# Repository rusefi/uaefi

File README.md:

# Ultra Affordable EFI

🟢[$275 base model rusEFI store](https://www.shop.rusefi.com/shop/p/uaefi-ultra-affordable-efi)🟢

## Community Support

🔴Community support ONLY 🔴 https://www.facebook.com/groups/rusEfi 🔴 [Discord](https://github.com/rusefi/rusefi/wiki/Discord)🔴 [Commercial Support](https://www.shop.rusefi.com/shop/p/details-about-rusefi-ecu-technical-support) 🔴

## Technical Details

Open Source KiCAD hardware powered by [Hellen-One](https://github.com/andreika-git/hellen-one)

Powered by [rusEFI firmware](https://github.com/rusefi/rusefi)

[User Documentation](https://github.com/rusefi/rusefi/wiki/uaEFI)

## MCU options

1mb of flash is _required_.

One day we shall try https://jlcpcb.com/partdetail/Stmicroelectronics-STM32F427VIT6%2FC57097#EC or https://jlcpcb.com/partdetail/Stmicroelectronics-STM32F437VIT7%2FC1338578#EC

## HOWTO JLCPCB

You would need three files from ``boards/uaefi-a/board`` folder to place your JLCPB Assembly order: gerber.zip BOM-JLC.csv and CPL.csv

### Q: having trouble with opening uaefi board project. library path seems ok, i do not know how to solve missing modules issue

A: missing modules are closed source. they are filled in by github magic
github magic combines gerbers and spits out a complete bom/pcl/new gerbers to upload to jlc/friends. See https://github.com/rusefi/hellen-one/tree/master?tab=readme-ov-file#tldr for more info

### Q: Magic modules? How do I see schematics of those?

A: https://github.com/rusefi/hellen-one has full documentation for each module

### Q: Something wrong with BOM?

A: Nope, that's normal nothing to worry about click 'Continue'.

### Q: how do I get more RAM for Lua?

A: fabricate with STM32F42xVI firmware would defect extra RAM and give you extra Lua. Once your script does not fit into STM32F42xVI it's F7 time or help us leverage F413.

### Q: I've place an order with JLCPCB and I see scary looking wrong orientation?

A: that's expected. See [boards/uaefi-c/board](boards/uaefi-c/board) ``Original*.png`` files and ``Produce*.png`` after JLCPCB manual review process.

## Bluetooth power issue fix

It was found that board with installed BT module may be affected by power issue.

During power on BT module consume too much inrush current on 3.3V line causing 3.3V drop below MCU reset hreshold. This may lead to unstable start or infinity reset loop.

To fix this please install additional capacitors to 5V and 3.3V powerlines.

Polarized electrolytic capacitors with at least 10V rating and extended temperature range are recommended. Tantalum and solid electrolytic capacitors are also suitable.

**Please carefully follow illustrated polarity.**

33..47uF should be added to 5V powerrail. [This](https://www.digikey.com/en/products/detail/w%C3%BCrth-elektronik/860020372004/5727028) or [this](https://www.digikey.com/en/products/detail/w%C3%BCrth-elektronik/860080372001/5727224) or [any of these](https://www.digikey.com/en/products/filter/aluminum-electrolytic-capacitors/58?s=N4IgjCBcpgbFoDGUBmBDANgZwKYBoQB7KAbRAGYBOAJnOoAYQBdAgBwBcoQBldgJwCWAOwDmIAL4FYlBCGSR02fEVIgALGDAAOSgHZmbTpB79hYyeEo7Z8xbgLFIZRkwsM1M6HNSZ7Kp%2Bq6AAQArQBiBiAcXACqQgLsAPIoALI4aFgArnw4EgQMup5IPkoOqnBBAGqR0cZxCclpGdm5FgC01DZQ-JnKjmQArMzibqpqwZkoQXAAbsNAA).

And 220..470uF should be added to 3.3V powerrail. [This](https://www.digikey.com/en/products/detail/w%C3%BCrth-elektronik/860010273011/5726952) or [this](https://www.digikey.com/en/products/detail/w%C3%BCrth-elektronik/860020273011/5727148) or [any of these](https://www.digikey.com/en/products/filter/aluminum-electrolytic-capacitors/58?s=N4IgjCBcpgbFoDGUBmBDANgZwKYBoQB7KAbRAGYBOAJnOoAYQBdAgBwBcoQBldgJwCWAOwDmIAL4FYlBCGSR02fEVIgALGDAAOSgHZmbTpB79hYyeEo7Z8xbgLFIZRkwsM1M6HNSZ7Kp%2Bq69AAEAK0AYgYgHFwAqkIC7ADyKACyOGhYAK58OBIEDLqeSD5KDqpgIQBqUTHG8Ykp6Zk5eRYAtNQ2UPxZyo5kAKzM4qNAA).

## HOWTO EGT chip

This board has a placeholder for MAX31855 (or MAX6675) termocouple-to-digital chip. **This chip is not populated by default!**

D8 is **optional** ESD protection and also is not populated by default. You need to solder U4 only, D8 is optional. All passive components are already populated.

**MAX31855** works without addtional modification.

For **MAX6675** connect EGT- to GNDA either on J2 "C" connector or just short C28 (replace with 0R).

## [EXPERIMENTAL] How to make MAX9924 work with low tooth count trigger wheel

In some cases user may need two VR inputs on UAEFI and both trigger wheels are low-tooth count.

In default configuration MAX9924 does not work with low count trigger wheels because of its "adaptive peak threshold" and its watchdog.

On UAEFI MAX9924 is configured in **A2 mode**.

**B mode** allow use of MAX9924 with low count trigger wheels. But external Bias and Thresholt voltages should be allpied. Both can be sources from UAEFI Discrete VR module.

List of modifications:
1. pin 6: ZERO_EN connect to VCC instead of GND.
2. pin 4: supply 2.5 V instead of GND
3. pin 8: EXT, supply external threshold voltage

Pins 4 and 6 needs to be lifted from PCB to be disconnected from GND. Pin 8 initially is not connected to any circuit.

Use hot air gun to de-solder whole chip. Then twist pins 4 and 6 up so both do not touch PCB. Then solder chip back to PCB

Now use thin wire to connect:
1. pin 6 to pin 10 of the same chip.
2. pin 4 to **Vref** at R769 + C754. See [iBOM](https://github.com/rusefi/uaefi/blob/main/boards/uaefi-d/board/uaefi-d-ibom.html) for its locations
3. pin 8 to **thresh_high** at U756 pin 1. See [iBOM](https://github.com/rusefi/uaefi/blob/main/boards/uaefi-d/board/uaefi-d-ibom.html) for its locations

Now MAX9924 VR input uses same threshold vs RPM settings that is set for Descrete VR input. And it is cabable to work with low tooth count trigger wheels without noise issues.

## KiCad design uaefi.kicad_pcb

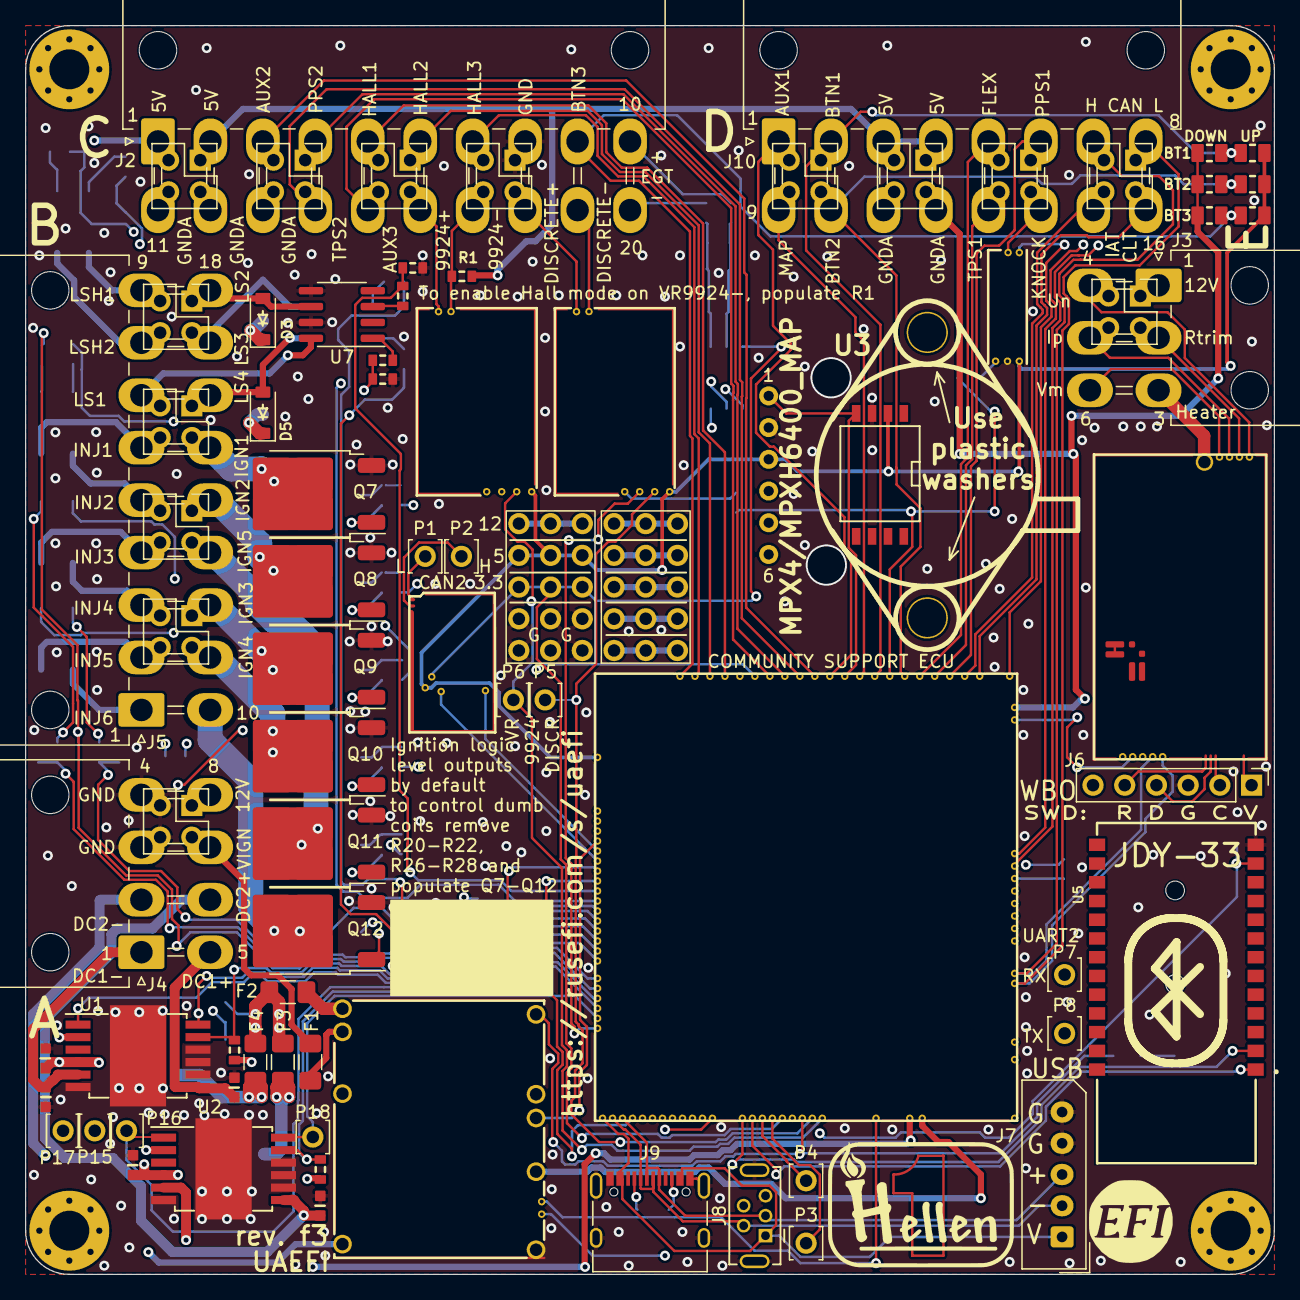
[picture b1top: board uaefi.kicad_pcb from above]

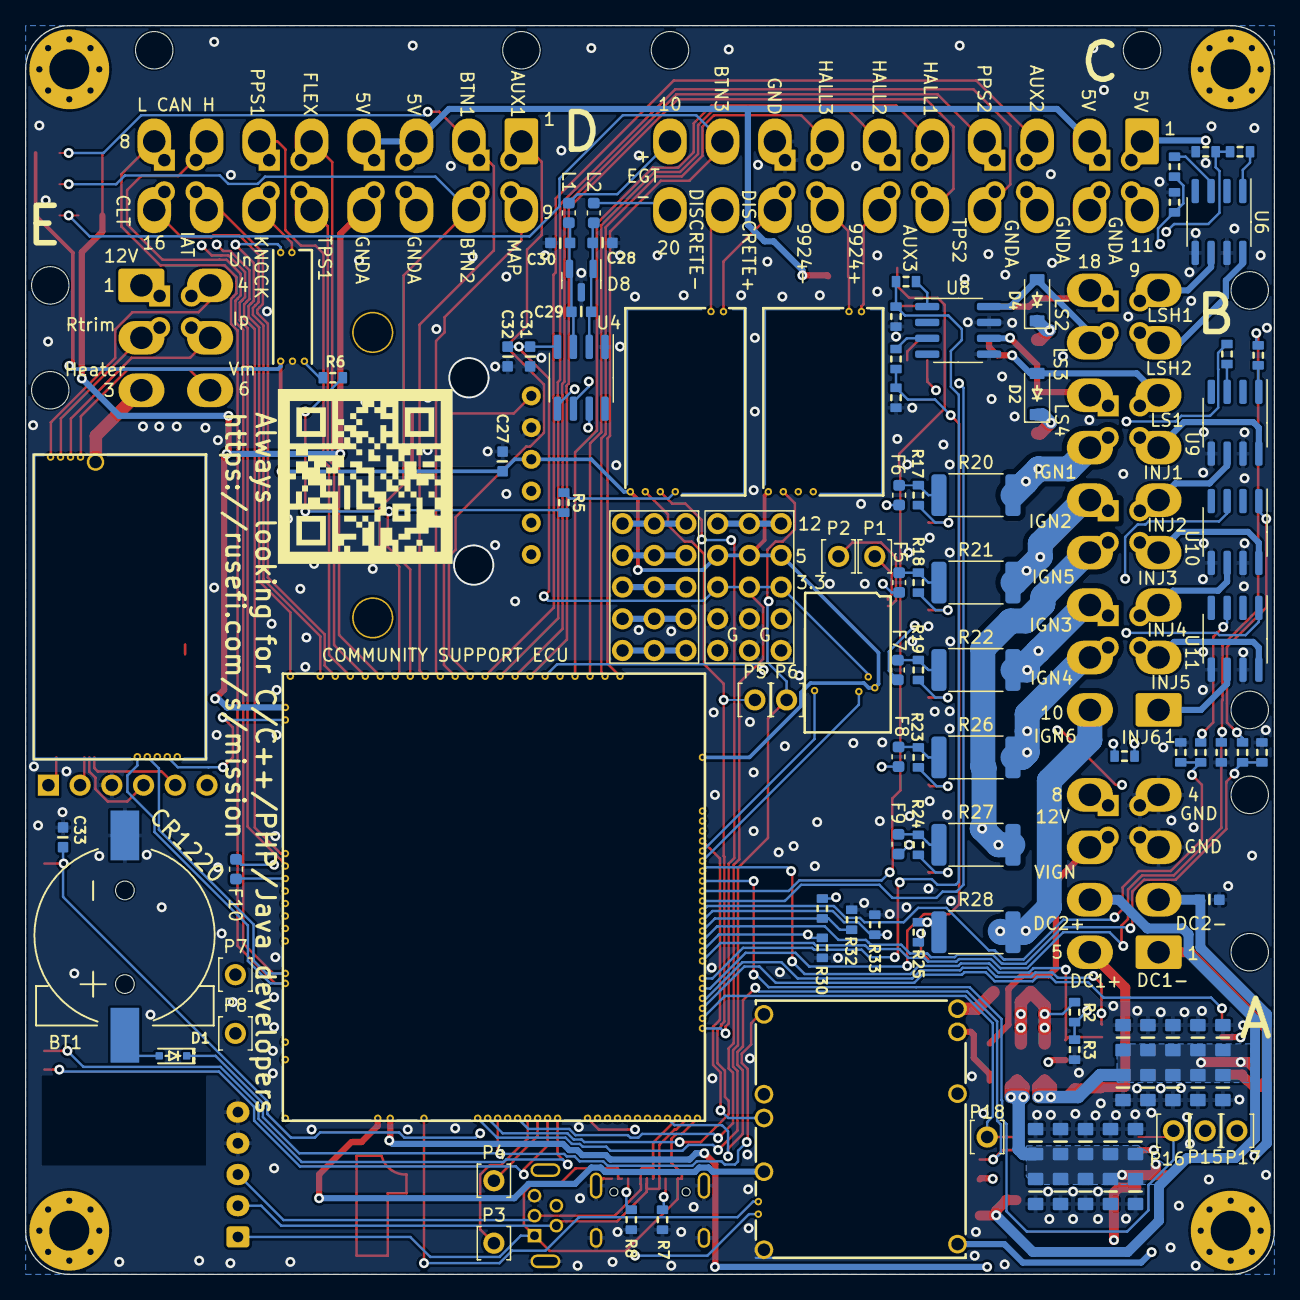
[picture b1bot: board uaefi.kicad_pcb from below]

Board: 4 copper layers, 100.0 x 100.0 mm, 170 parts (85 on the bottom side), 156 nets.

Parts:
BT1: CR1220; CR1220-2
C1, C2, C3, C4, C5, C6, C7, C8, C9, C10, C14, C15, C16, C17, C18, C19, C20, C21, C22, C23: 10u; C0805
C11, C24, C27, C29, C31, C33: 100n; C0603
C12, C13, C25, C26, C28, C30: 10n; C0603
C32: 1u; C0603
D1: 1N4148WS; SOD-323
D2, D3, D4, D5: B5819W; SOD-123
D8: NUP2105L; SOT-23
F1, F2, F3, F4: Fuse; Fuse_1206_3216Metric_Pad1.42x1.75mm_HandSolder
F5, F6, F7, F8, F9, F10: 50mA; Fuse_0603_1608Metric
G1: RUSEFI_LOGO; rusefi_logo
G2: LOGO
G3, G4: PROTO_AREA
H1, H2, H3, H4: M3; MountingHole_3.2mm_M3_Pad_Via
J1, J11, J12, J13, J14, J15, J16, J17, J18, J19, J20, J21, J22, J24: Conn_02x02_Odd_Even; PinSocket_2x02_P2.54mm_Vertical
J2: 5569-20A2; Molex_Mini-Fit_Jr_5569-20A2_2x10_P4.20mm_Horizontal
J3: 5569-06A2; Molex_Mini-Fit_Jr_5569-06A2_2x03_P4.20mm_Horizontal
J4: 5569-08A2; Molex_Mini-Fit_Jr_5569-08A2_2x04_P4.20mm_Horizontal
J5: 5569-18A2; Molex_Mini-Fit_Jr_5569-18A2_2x09_P4.20mm_Horizontal
J6: Conn_01x06; PinHeader_1x06_P2.54mm_Vertical
J7: Conn_01x05_Male; Molex_SPOX_5267-05A_1x05_P2.50mm_Vertical
J8: USB_B_Mini; USB-MINI-B-VERTICAL
J9: USB_C
J10: 5569-16A2; Molex_Mini-Fit_Jr_5569-16A2_2x08_P4.20mm_Horizontal
L1, L2: 470R@100MHz; L_0603_1608Metric
M1: Module-power_12and5V-0.3; power_12and5V
M2: Module-knock-0.2; knock
M3: Module-vr-discrete-0.5; vr-discrete
M4: Module-vr-max9924-0.1; vr-max9924
M5: Module-wbo-0.6; wbo
M6: Module:mega-mcu100/0.3; mega-mcu100
M7: Module-can-0.1; can
P1, P2, P3, P4, P5, P6, P7, P8, P15, P16, P17, P18: Pad; PAD-TH
Q7, Q8, Q9, Q10, Q11, Q12: ISL9V3040D3ST; TO-252-2
R1, R4, R9, R10, R11, R12, R13, R14, R15, R16, R29, R30, R31, R32, R33, R34, R41, R42, R43, R44, R45, R46, R47, R48, R49, R50, R51: 4.7k; R0603
R2: 33k; R0603
R3: 6.8k; R0603
R5, R6: 0; R0603
R7, R8: 5.6k; R0603
R17, R18, R19, R23, R24, R25: 22; R0603
R20, R21, R22, R26, R27, R28: 0; R_2512_6332Metric
R35, R36, R37: 10k; R0805
R38, R39, R40: DNP; R0805
U1, U2: TLE9201SG; Infineon_PG-DSO-12-11
U3: MPX4/MPXH6400_MAP; MPX-4_MAP
U4: MAX31855KASA; SOIC-8_3.9x4.9mm_P1.27mm
U5: JDY-33
U6, U7, U8, U9, U10, U11: VNLD5160TR-E; SOIC-8_3.9x4.9mm_P1.27mm

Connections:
+3.3V: M6.N21 (V33), R9.2, R14.2, U1.2 (VSO), U2.2 (VSO)
+3.3VA: C31.2, C32.2, C33.2, G3.3, G3.8, G3.13, M6.N15 (V33_SWITCHABLE), M7.V2 (CAN_VIO), U4.4 (V_{CC}), U5.12 (3V3)
+5V: M1.E4 (V5), M6.N22 (VCC)
+5VA: C27.2, G3.4, G3.9, G3.14, M2.E1 (V5A), M3.E4 (V5_IN), M4.E4 (V5_IN), M5.W1 (V5_IN), M6.E1 (V5A_SWITCHABLE), M6.W2 (V5A_SWITCHABLE), M7.V1 (V5), R38.2, R39.2, R40.2, U3.3 (VCC)
+5VP: J2.1, J2.2, J10.3, J10.4, J12.1, J12.2, J14.1, J14.2, M1.V4 (5VP), R1.1
+12V: F2.1, F3.1, F4.1, J4.8, J22.1, R2.2
+12V_RAW: D2.1 (K), D3.1 (K), D4.1 (K), D5.1 (K), F2.2, G3.5, G3.10, G3.15, J3.1, J24.1, M1.V1 (V12_PERM), M1.V3 (V12_RAW)
/1_WBO_Ip: J3.5, J24.4, M5.E3 (LSU_Ip)
/2_WBO_Vm: J3.6, M5.E2 (LSU_Vm)
/3_WBO_Heater: J3.3, M5.E5 (LSU_Htr)
/5_WBO_Rtrim: J3.2, J24.3, M5.E4 (LSU_Rtrim)
/6_WBO_Un: J3.4, J24.2, M5.E1 (LSU_Un)
/12V_KEY: F1.1, J4.7, J22.3
/ADC3: M6.S15 (IN_KNOCK_(PA2)), R5.2, R6.2
/CAN+: J1.2, J10.7, M5.W4 (CANH), M6.W11 (CANH)
/CAN-: J1.1, J10.8, M5.W3 (CANL), M6.W12 (CANL)
/DC1_DIR: M6.E21 (OUT_PWM4_(PC8)), P15.1, U1.1 (DIR)
/DC1_DIS: M6.E8 (SPI2_MISO_(PB14)), R9.1, U1.11 (DIS)
/DC1_PWM: M6.E20 (OUT_PWM3_(PC7)), P17.1, U1.12 (PWM)
/DC2_DIR: M6.E9 (SPI2_MOSI_(PB15)), P16.1, U2.1 (DIR)
/DC2_DIS: M6.N4 (USBID_(PA10)), R14.1, U2.11 (DIS)
/DC2_PWM: M6.E22 (OUT_PWM5_(PC9)), P18.1, U2.12 (PWM)
/DC Driver 1/PWR: C1.2, C2.2, C3.2, C4.2, C5.2, C6.2, C7.2, C8.2, C9.2, C10.2, C11.2, F4.2, U1.4 (VS)
/DC Driver 2/PWR: C14.2, C15.2, C16.2, C17.2, C18.2, C19.2, C20.2, C21.2, C22.2, C23.2, C24.2, F3.2, U2.4 (VS)
/EGT+: J2.10, L1.1
/EGT-: J2.20, L2.1
/EGT/SPI_CS: M6.N9 (SPI3_CS_(PA15)), U4.6 (~CS)
/IGN1: F6.2, M6.W10 (IGN1_(PC13))
/IGN2: F5.2, M6.W9 (IGN2_(PE5))
/IGN3: F7.2, M6.W8 (IGN3_(PE4))
/IGN4: F8.2, M6.W7 (IGN4_(PE3))
/IGN5: F9.2, M6.W6 (IGN5_(PE2))
/IGN6: F10.2, M6.W5 (IGN6_(PB8))
/INJ1: M6.E17 (OUT_INJ1_(PD3)), R29.2, R42.1
/INJ2: M6.E16 (OUT_INJ2_(PA9)), R30.2, R43.1
/INJ3: M6.E15 (OUT_INJ3_(PD11)), R31.2, R44.1
/INJ4: M6.E14 (OUT_INJ4_(PD10)), R32.2, R45.1
/INJ5: M6.E13 (OUT_INJ5_(PD2)), R33.2, R46.1
/INJ6: M6.E12 (OUT_INJ6_(PA8)), R34.2, R47.1
/INTERNAL_MAP: M6.S12 (IN_MAP2_(PC1)), U3.1 (VOUT)
/IN_AUX1: J10.1, J13.2, M6.S11 (IN_O2S_/_CAN_WAKEUP_(PA0))
/IN_AUX2: J2.3, J15.2, M6.S10 (IN_O2S2_(PA1))
/IN_AUX3: J2.15, J16.4, M6.S7 (IN_AUX3_(PA7))
/IN_BUTTON1: J10.2, J13.1, M6.S14 (IN_CRANK_(PB1)), R35.2, R38.1
/IN_BUTTON2: J10.10, J13.3, M6.S16 (IN_CAM_(PA6)), R36.2, R39.1
/IN_BUTTON3: J2.9, M6.S1 (IN_D4_(PE15)), R37.2, R40.1
/IN_CLT: J1.3, J10.16, M6.S21 (IN_CLT_(PC2))
/IN_FLEX: J10.5, J11.2, M6.S17 (IN_VSS_(PE11))
/IN_HALL1: J2.5, J16.2, M6.S4 (IN_D1_(PE12))
/IN_HALL2: J2.6, J16.1, M6.S3 (IN_D2_(PE13))
/IN_HALL3: J2.7, J17.2, M6.S2 (IN_D3_(PE14))
/IN_IAT: J1.4, J10.15, M6.S20 (IN_IAT_(PC3))
/IN_KNOCK: M2.E3 (OUT_KNOCK), R6.1
/IN_KNOCK_RAW: J10.14, J11.3, M2.W1 (IN_KNOCK)
/IN_MAP: J10.9, J13.4, M6.S13 (IN_MAP1_(PC0))
/IN_PPS1: J10.6, J11.1, M6.S19 (IN_PPS_(PA3))
/IN_PPS2: J2.4, J15.1, M6.S8 (IN_AUX2_(PC4/PE9))
/IN_TPS1: J10.13, J11.4, M6.S18 (IN_TPS_(PA4))
/IN_TPS2: J2.14, J15.3, M6.S9 (IN_AUX1_(PB0))
/IN_VIGN: F1.2, M1.V2 (IN_VIGN)
/IN_VMAIN: M6.S6 (IN_AUX4_(PC5)), R2.1, R3.2
/LS1: M6.E11 (OUT_INJ7_(PD15)), R10.2, R48.1
/LS2: M6.E10 (OUT_INJ8_(PD12)), R11.2, R49.1
/LS3: M6.E18 (OUT_PWM1_(PD13)), R12.2, R50.1
/LS4: M6.E19 (OUT_PWM2_(PC6)), R13.2, R51.1
/LS_HOT1: M6.W4 (IGN7_(PB9)), R16.1, R41.1
/LS_HOT2: M6.W3 (IGN8_(PE6)), R4.1, R15.1
/MISO3: M6.N11 (SPI3_MISO_(PC11)), U4.7 (SO)
/OUT_DC1+: C13.2, J4.5, U1.7 (OUT2)
/OUT_DC1-: C12.2, J4.1, U1.5 (OUT1)
/OUT_DC2+: C26.2, J4.6, U2.7 (OUT2)
/OUT_DC2-: C25.2, J4.2, U2.5 (OUT1)
/OUT_IGN1: J5.15, J19.3, Q7.2 (C), R20.2
/OUT_IGN2: J5.14, J20.1, Q8.2 (C), R21.2
/OUT_IGN3: J5.12, J21.1, Q9.2 (C), R22.2
/OUT_IGN4: J5.11, J21.3, Q10.2 (C), R26.2
/OUT_IGN5: J5.13, J20.3, Q11.2 (C), R27.2
/OUT_IGN6: J5.10, Q12.2 (C), R28.2
/OUT_INJ1: J5.6, J19.4, U9.8 (D1)
/OUT_INJ2: J5.5, J20.2, U9.6 (D2)
/OUT_INJ3: J5.4, J20.4, U10.8 (D1)
/OUT_INJ4: J5.3, J21.2, U10.6 (D2)
/OUT_INJ5: J5.2, J21.4, U11.8 (D1)
/OUT_INJ6: J5.1, U11.6 (D2)
/OUT_LS1: D2.2 (A), J5.7, J19.2, U7.8 (D1)
/OUT_LS2: D3.2 (A), J5.18, J18.1, U7.6 (D2)
/OUT_LS3: D4.2 (A), J5.17, J18.3, U8.8 (D1)
/OUT_LS4: D5.2 (A), J5.16, J19.1, U8.6 (D2)
/OUT_LS_HOT1: J5.9, J18.2, U6.6 (D2)
/OUT_LS_HOT2: J5.8, J18.4, U6.8 (D1)
/PG_5VP: M1.E6 (PG_5VP), M6.N12 (SPI3_MOSI_(PC12))
/PWR_EN: M1.E5 (EN_5VP), M6.N20 (OUT_PWR_EN_(PE10))
/SCK3: M6.N10 (SPI3_SCK_(PC10)), U4.5 (SCK)
/USB+: J7.3, J8.3 (D+), J9.A6 (D+), J9.B6 (D+), M6.N3 (USBP_(PA12))
/USB-: J7.2, J8.2 (D-), J9.A7 (D-), J9.B7 (D-), M6.N2 (USBM_(PA11))
/VBAT: D1.1 (K), M1.E1 (VBAT), M6.N17 (VBAT)
/VBUS: J7.1, J8.1 (VBUS), J9.A4 (VBUS), J9.A9 (VBUS), J9.B4 (VBUS), J9.B9 (VBUS), M6.N1 (VBUS)
/VIGN: M1.E3 (VIGN), M6.E5 (IN_VIGN_(PA5))
/VREF1: M2.W2 (VREF), M6.S22 (VREF1)
/VR_DISCRETE: M3.E3 (OUT), M6.N18 (UART8_RX_(PE0)), P5.1
/VR_DISCRETE+: J2.18, J17.3, M3.W2 (VR+)
/VR_DISCRETE-: J2.19, M3.W1 (VR-)
/VR_DISCRETE_A: M3.E2 (OUT_A), R5.1
/VR_DISCRETE_THR: M3.E1 (Thresh_IN), M6.E23 (OUT_PWM6_(PD14))
/VR_MAX9924: M4.E3 (OUT), M6.N19 (UART8_TX_(PE1)), P6.1
/VR_MAX9924+: J2.16, J16.3, M4.W2 (VR+)
/VR_MAX9924-: J2.17, J17.4, M4.W1 (VR-), R1.2
GND: BT1.2 (-), C1.1, C2.1, C3.1, C4.1, C5.1, C6.1, C7.1, C8.1, C9.1, C10.1, C11.1, C12.1, C13.1, C14.1, C15.1, C16.1, C17.1, C18.1, C19.1, C20.1, C21.1, C22.1, C23.1, C24.1, C25.1, C26.1, C27.1, C28.1, C30.1, C31.1, C32.1, C33.1, D8.3 (A), G3.1, G3.2, G3.6, G3.7, G3.11, G3.12, J2.8, J4.3, J4.4, J6.3, J7.4, J7.5, J8.5 (GND), J8.6 (Shield), J9.A1 (GND), J9.A12 (GND), J9.B1 (GND), J9.B12 (GND), J9.S1 (SHIELD), J17.1, J22.2, J22.4, M1.S1 (GND), M2.E2 (GND), M3.G (GND), M4.G (GND), M5.G (GND), M6.G (GND), M7.E1 (GND), Q7.3 (E), Q8.3 (E), Q9.3 (E), Q10.3 (E), Q11.3 (E), Q12.3 (E), R3.1, R7.1, R8.1, R10.1, R11.1, R12.1, R13.1, R15.2, R16.2, R29.1, R30.1, R31.1, R32.1, R33.1, R34.1, U1.6 (GND), U1.8 (SI), U1.9 (CSN), U1.10 (SCK), U1.13 (GND), U2.6 (GND), U2.8 (SI), U2.9 (CSN), U2.10 (SCK), U2.13 (GND), U3.2 (GND), U4.1 (GND), U5.13 (GND), U6.5 (S2), U6.7 (S1), U7.5 (S2), U7.7 (S1), U8.5 (S2), U8.7 (S1), U9.5 (S2), U9.7 (S1), U10.5 (S2), U10.7 (S1), U11.5 (S2), U11.7 (S1)
GNDA: J2.11, J2.12, J2.13, J10.11, J10.12, J12.3, J12.4, J14.3, J14.4, J15.4, M6.W1 (GNDA), R35.1, R36.1, R37.1
unnamed: BT1.1 (+), D1.2 (A)
unnamed: F5.1, R18.2, R21.1
unnamed: F6.1, R17.2, R20.1
unnamed: F7.1, R19.2, R22.1
unnamed: F8.1, R23.2, R26.1
unnamed: F9.1, R24.2, R27.1
unnamed: F10.1, R25.2, R28.1
unnamed: G4.1, G4.6, G4.11
unnamed: G4.5, G4.10, G4.15
unnamed: G4.2, G4.7, G4.12
unnamed: G4.3, G4.8, G4.13
unnamed: G4.4, G4.9, G4.14
unnamed: J6.1, M5.W8 (V33_OUT)
unnamed: J6.2, M5.W7 (SWCLK)
unnamed: J6.4, M5.W6 (SWDIO)
unnamed: J6.5, M5.W5 (nReset)
unnamed: J9.A5 (CC1), R7.2
unnamed: J9.B5 (CC2), R8.2
unnamed: M5.J1 (SEL1), M5.J_GND1 (PULL_DOWN1)
unnamed: M6.N14a (LED_GREEN), P4.1
unnamed: M6.N14b (LED_YELLOW), P3.1
unnamed: M6.E6 (SPI2_CS_/_CAN2_RX_(PB12)), M7.V6 (CAN_RX)
unnamed: M6.E7 (SPI2_SCK_/_CAN2_TX_(PB13)), M7.V5 (CAN_TX)
unnamed: M6.N14 (UART2_RX_(PD6)), P7.1, U5.1 (TXD)
unnamed: M6.N13 (UART2_TX_(PD5)), P8.1, U5.2 (RXD)
unnamed: M7.S2 (CANH), P2.1
unnamed: M7.S1 (CANL), P1.1
unnamed: Q7.1 (G), R17.1
unnamed: Q8.1 (G), R18.1
unnamed: Q9.1 (G), R19.1
unnamed: Q10.1 (G), R23.1
unnamed: Q11.1 (G), R24.1
unnamed: Q12.1 (G), R25.1
unnamed: C29.2, C30.2, D8.2 (K), L1.2, U4.3 (T+)
unnamed: C28.2, C29.1, D8.1 (K), L2.2, U4.2 (T-)
unnamed: R4.2, U6.1 (IN1)
unnamed: R41.2, U6.3 (IN2)
unnamed: R48.2, U7.1 (IN1)
unnamed: R49.2, U7.3 (IN2)
unnamed: R50.2, U8.1 (IN1)
unnamed: R51.2, U8.3 (IN2)
unnamed: R42.2, U9.1 (IN1)
unnamed: R43.2, U9.3 (IN2)
unnamed: R44.2, U10.1 (IN1)
unnamed: R45.2, U10.3 (IN2)
unnamed: R46.2, U11.1 (IN1)
unnamed: R47.2, U11.3 (IN2)

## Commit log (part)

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2023-09-11 stub
2023-11-13 Upd SCH
2023-11-29 [skip actions] Auto-generated board
2023-11-30 #6, #7, #8, #9
2023-11-30 Placement
2023-12-02 Export
2023-12-02 Shortage fix
2023-12-02 Upd PCB
2023-12-03 #18 #19 #20
2023-12-03 ordered
2023-12-04 review fab files #21
2023-12-04 BOM substitutions
2023-12-07 magic
2023-12-16 docs
2023-12-22 store pics
2023-12-22 same thing just without connectors
2023-12-22 updating LEDs
2024-01-12 https://github.com/rusefi/uaefi/issues/31
2024-01-12 as-is copy
2024-01-12 in progress
2024-01-13 C117, C123 fix again #32
2024-01-13 cost reduction ideas #35
2024-01-15 more current Q
2024-01-26 https://github.com/rusefi/uaefi/issues/23
2024-02-03 crimp kit
2024-02-05 [skip actions] Auto-generated board v2.1
2024-02-06 Upd SCH, PCB
2024-02-06 L420 shortage
2024-02-06 just a copy
2024-02-06 without molex
2024-02-06 Blue 0402 LEDs shortage
2024-02-08 fab B U107 orientation #46
2024-02-27 more of same
2024-03-05 orange!
2024-03-27 Rev C
2024-04-05 Update submodules
2024-04-05 rev C no molex BOM
2024-04-05 DNP BLUETOOTH JDY
2024-04-08 fab C
2024-04-09 dates
2024-04-16 GHA says update hellen-one
2024-04-16 daily update
2024-05-07 comfort
2024-05-09 orientation files
2024-06-20 BOM update
2024-08-15 #62 #65 #66 #67 #53
2024-08-16 fab D
2024-12-16 rev D no molex
2025-04-30 Rev E
2025-04-30 U110 warning fix
2025-05-15 rev E BOM copy without molex
2025-09-08 #81 #82 #86 #87
2025-09-08 no-molex
2025-09-10 no molex
2025-09-29 commercial support
2025-09-29 not 7, right? or is it 7.
    typo
2025-10-01 YELLOW_LED
2025-10-12 HowTo switch MAX9924 to B mode
2025-10-16 https://github.com/rusefi/hellen-private/issues/32#issuecomment-3410483581
2025-10-21 Revise capacitor values and add product links
    Updated capacitor recommendations for power rails with links.
2025-12-03 #102
2025-12-26 rebuild BOM
2025-12-26 restoring no-molex
2026-02-21 Update README with GitHub links for clarity
    Updated links in instructions to point to the iBOM on GitHub.
2026-03-22 #106 #107 rev e2
2026-04-03 Update hellen-one
2026-04-05 https://github.com/andreika-git/hellen-one/issues/395
2026-04-06 push poke
